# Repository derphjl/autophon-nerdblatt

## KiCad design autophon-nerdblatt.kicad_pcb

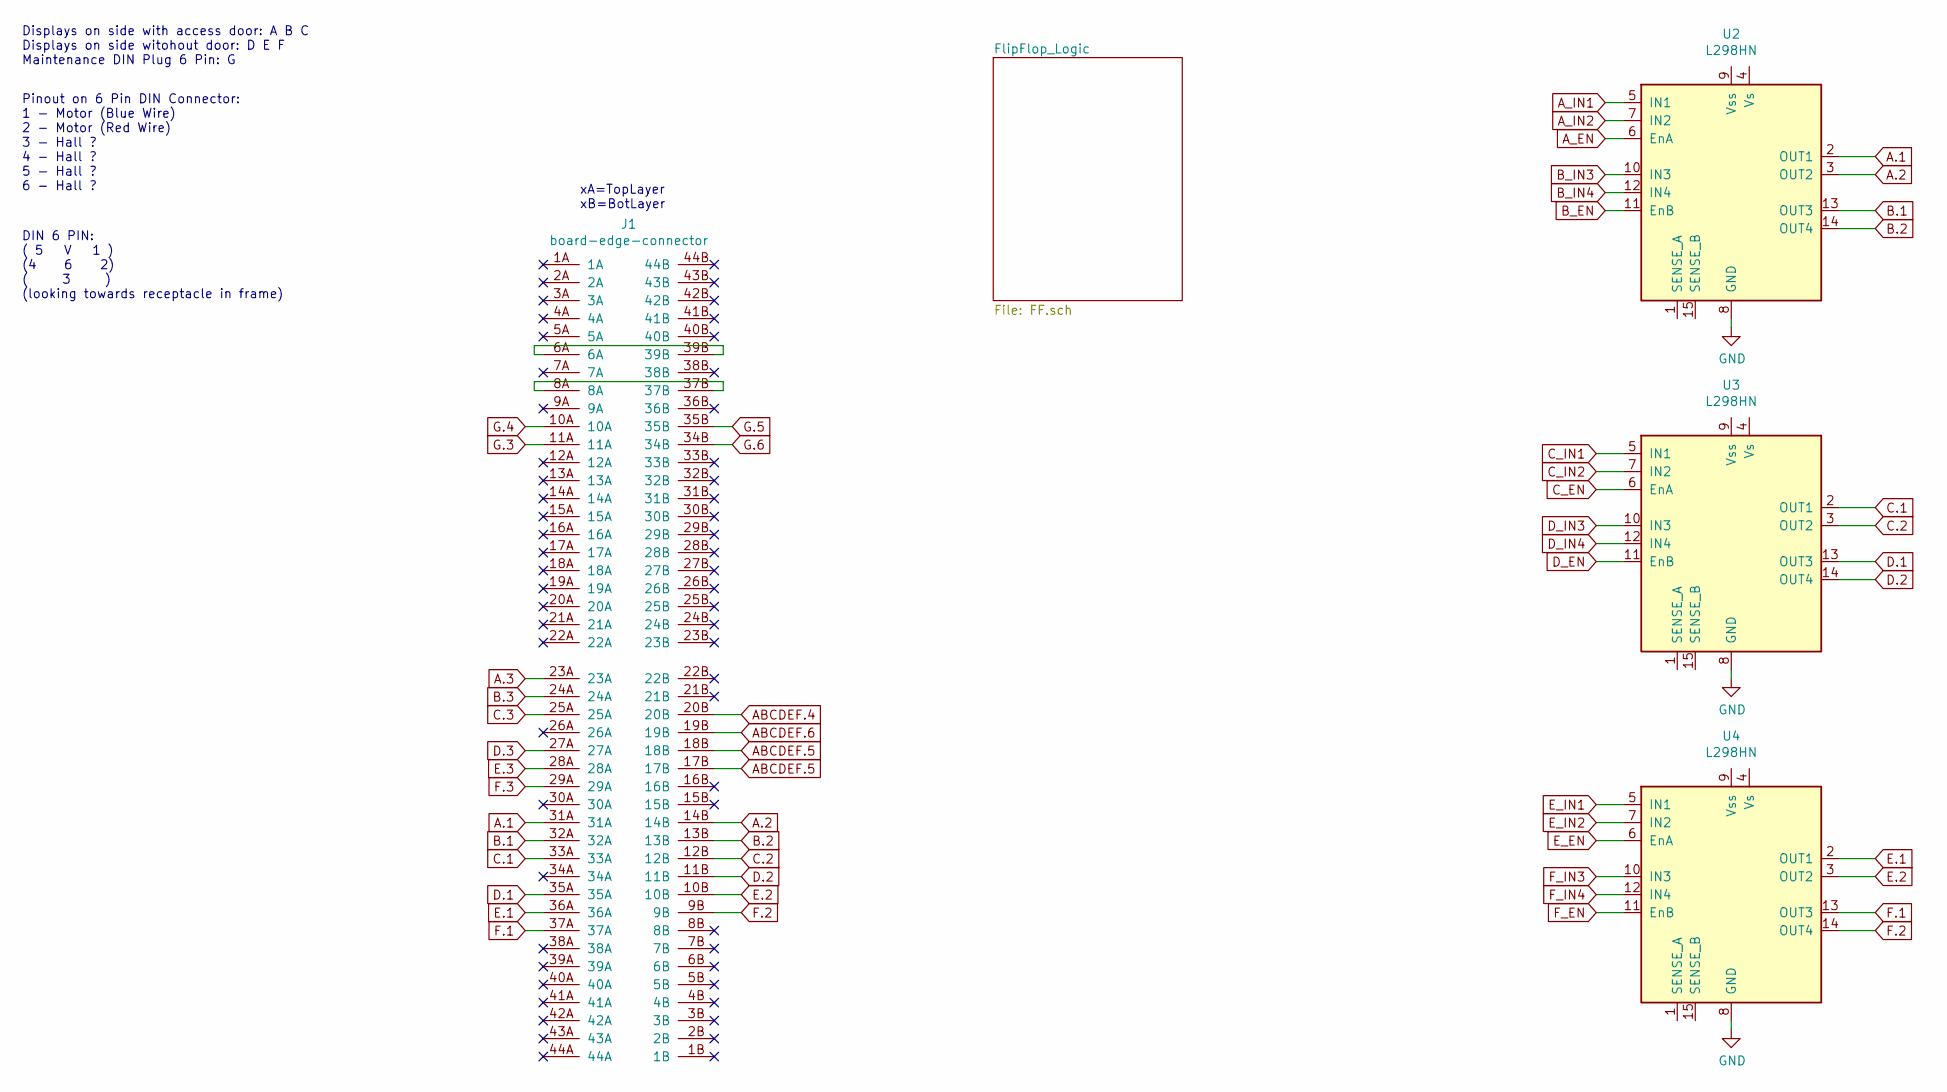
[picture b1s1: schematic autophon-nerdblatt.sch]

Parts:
J1: board-edge-connector; autophon-pcb-edge-connector
U2, U3, U4: L298HN; TO-220F-15_P2.54x5.08mm_StaggerOdd_Lead5.08mm_Vertical

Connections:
A.1: J1.31A, U2.2 (OUT1)
A.2: J1.14B, U2.3 (OUT2)
A.3: J1.23A
ABCDEF.4: J1.20B
ABCDEF.5: J1.17B, J1.18B
ABCDEF.6: J1.19B
A_EN: U2.6 (EnA)
A_IN1: U2.5 (IN1); also elsewhere on the board
A_IN2: U2.7 (IN2); also elsewhere on the board
B.1: J1.32A, U2.13 (OUT3)
B.2: J1.13B, U2.14 (OUT4)
B.3: J1.24A
B_EN: U2.11 (EnB)
B_IN3: U2.10 (IN3); also elsewhere on the board
B_IN4: U2.12 (IN4); also elsewhere on the board
C.1: J1.33A, U3.2 (OUT1)
C.2: J1.12B, U3.3 (OUT2)
C.3: J1.25A
C_EN: U3.6 (EnA)
C_IN1: U3.5 (IN1); also elsewhere on the board
C_IN2: U3.7 (IN2); also elsewhere on the board
D.1: J1.35A, U3.13 (OUT3)
D.2: J1.11B, U3.14 (OUT4)
D.3: J1.27A
D_EN: U3.11 (EnB)
D_IN3: U3.10 (IN3); also elsewhere on the board
D_IN4: U3.12 (IN4); also elsewhere on the board
E.1: J1.36A, U4.2 (OUT1)
E.2: J1.10B, U4.3 (OUT2)
E.3: J1.28A
E_EN: U4.6 (EnA)
E_IN1: U4.5 (IN1); also elsewhere on the board
E_IN2: U4.7 (IN2); also elsewhere on the board
F.1: J1.37A, U4.13 (OUT3)
F.2: J1.9B, U4.14 (OUT4)
F.3: J1.29A
F_EN: U4.11 (EnB)
F_IN3: U4.10 (IN3); also elsewhere on the board
F_IN4: U4.12 (IN4); also elsewhere on the board
G.3: J1.11A
G.4: J1.10A
G.5: J1.35B
G.6: J1.34B
GND: U2.8 (GND), U3.8 (GND), U4.8 (GND); also elsewhere on the board
unnamed: J1.8A, J1.37B
unnamed: J1.6A, J1.39B

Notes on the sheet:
Displays on side with access door: A B C Displays on side witohout door: D E F Maintenance DIN Plug 6 Pin: G
Pinout on 6 Pin DIN Connector: 1 - Motor (Blue Wire) 2 - Motor (Red Wire) 3 - Hall ? 4 - Hall ? 5 - Hall ? 6 - Hall ?
DIN 6 PIN: ( 5 V 1 ) (4 6 2) ( 3 ) (looking towards receptacle in frame)
xA=TopLayer xB=BotLayer

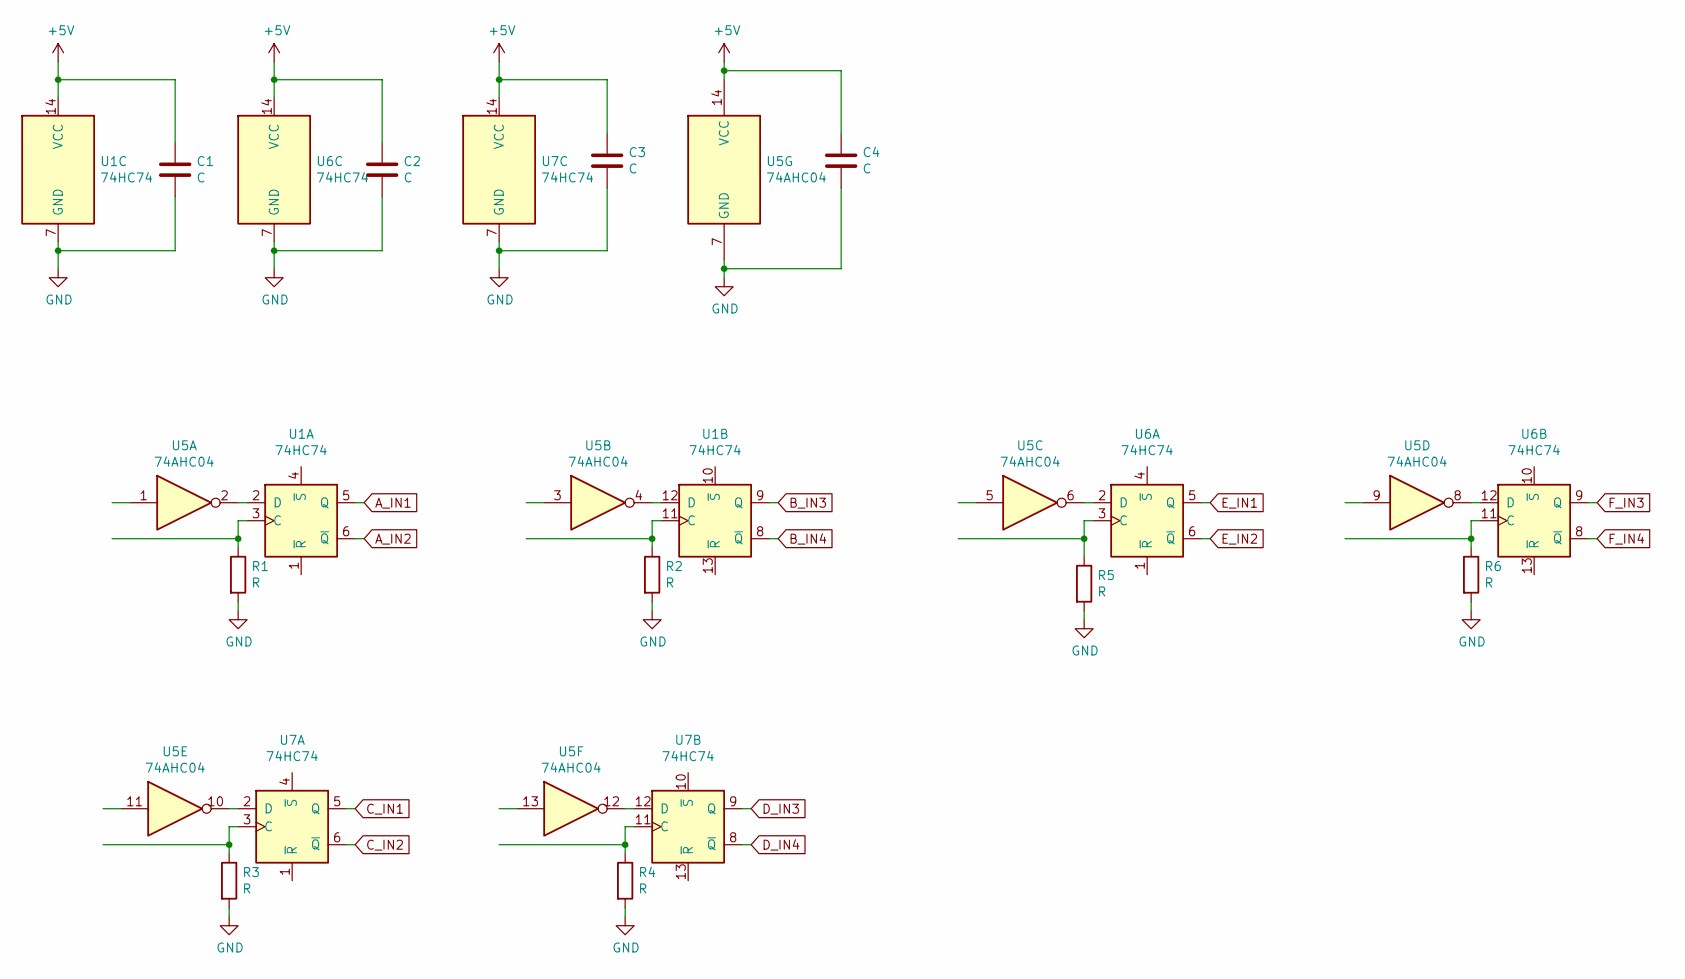
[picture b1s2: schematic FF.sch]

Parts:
C1, C2, C3, C4: C; C_0603_1608Metric
R1, R2, R3, R4, R5, R6: R; R_0603_1608Metric
U1, U6, U7: 74HC74; SO-14_5.3x10.2mm_P1.27mm
U5: 74AHC04; SO-14_5.3x10.2mm_P1.27mm

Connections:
+5V: C1.1, C2.1, C3.1, C4.1, U1.14 (VCC), U5.14 (VCC), U6.14 (VCC), U7.14 (VCC)
A_IN1: U1.5 (Q); also elsewhere on the board
A_IN2: U1.6 (~Q); also elsewhere on the board
B_IN3: U1.9 (Q); also elsewhere on the board
B_IN4: U1.8 (~Q); also elsewhere on the board
C_IN1: U7.5 (Q); also elsewhere on the board
C_IN2: U7.6 (~Q); also elsewhere on the board
D_IN3: U7.9 (Q); also elsewhere on the board
D_IN4: U7.8 (~Q); also elsewhere on the board
E_IN1: U6.5 (Q); also elsewhere on the board
E_IN2: U6.6 (~Q); also elsewhere on the board
F_IN3: U6.9 (Q); also elsewhere on the board
F_IN4: U6.8 (~Q); also elsewhere on the board
GND: C1.2, C2.2, C3.2, C4.2, R1.2, R2.2, R3.2, R4.2, R5.2, R6.2, U1.7 (GND), U5.7 (GND), U6.7 (GND), U7.7 (GND); also elsewhere on the board
unnamed: R1.1, U1.3 (C)
unnamed: R2.1, U1.11 (C)
unnamed: R3.1, U7.3 (C)
unnamed: R4.1, U7.11 (C)
unnamed: R5.1, U6.3 (C)
unnamed: R6.1, U6.11 (C)
unnamed: U1.2 (D), U5.2
unnamed: U1.12 (D), U5.4
unnamed: U5.6, U6.2 (D)
unnamed: U5.8, U6.12 (D)
unnamed: U5.10, U7.2 (D)
unnamed: U5.12, U7.12 (D)

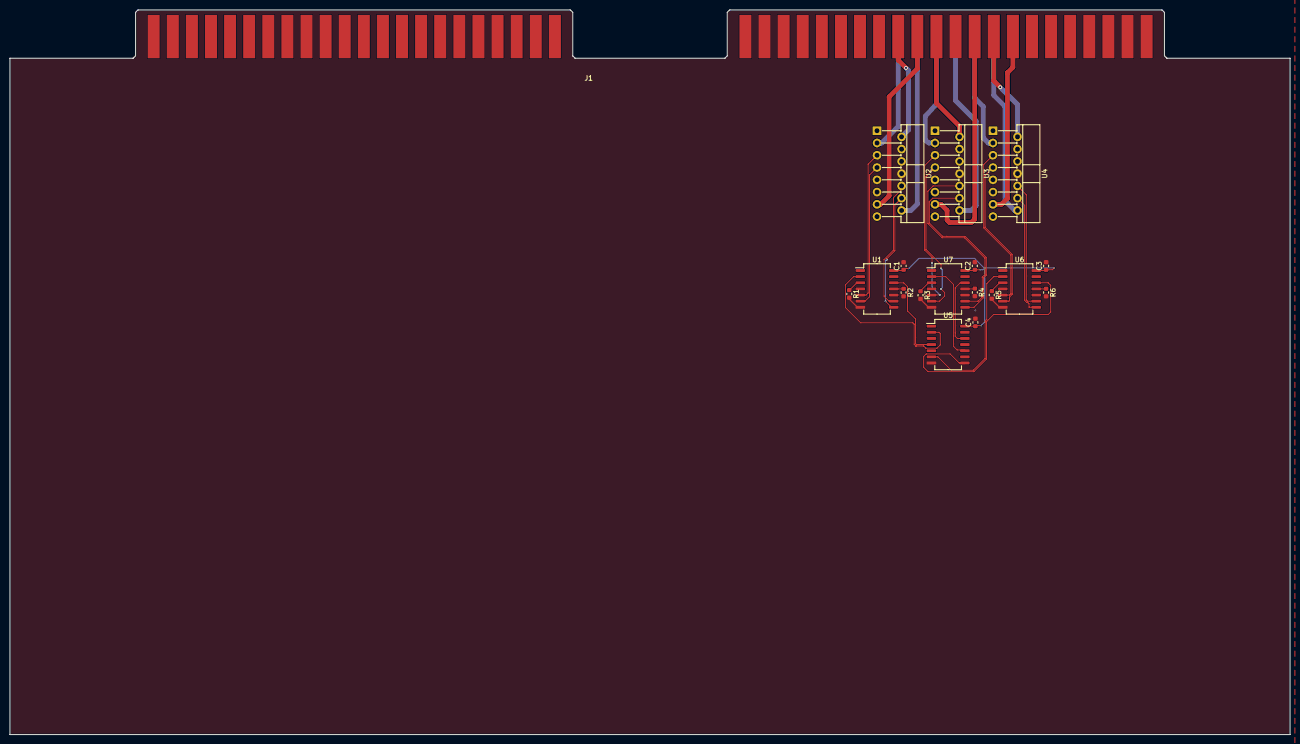
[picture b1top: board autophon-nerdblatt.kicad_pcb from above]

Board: 2 copper layers, 265.0 x 150.0 mm, 18 parts (0 on the bottom side), 41 nets.

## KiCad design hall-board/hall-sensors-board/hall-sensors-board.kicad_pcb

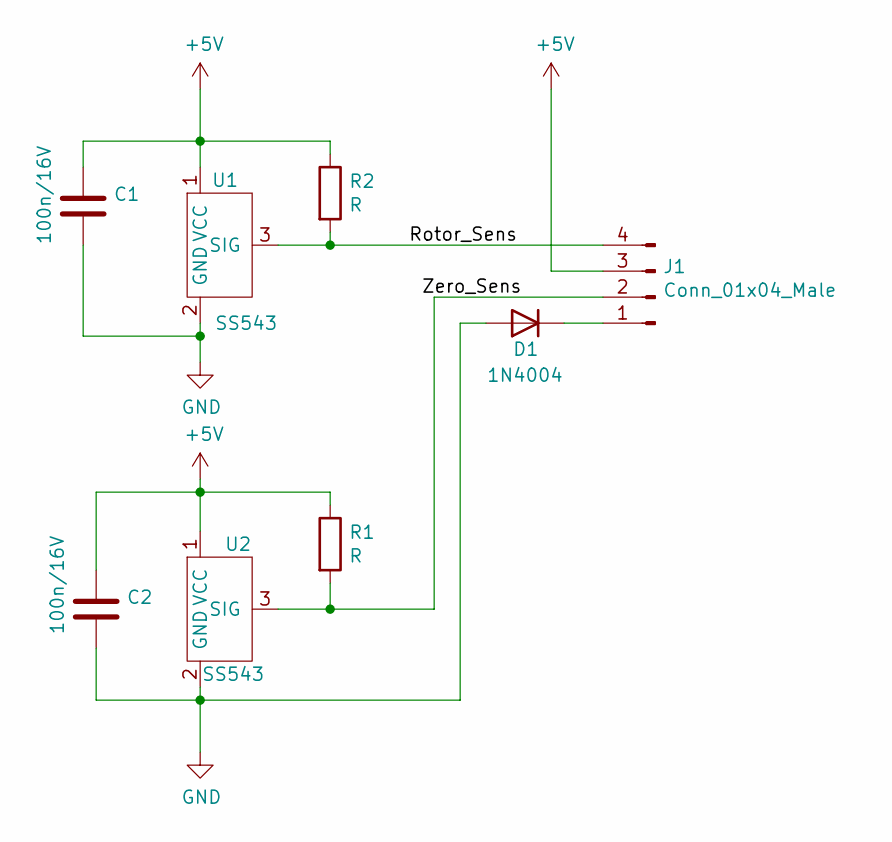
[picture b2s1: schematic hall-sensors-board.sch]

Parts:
C1, C2: 100n/16V; C_0603_1608Metric
D1: 1N4004; D_MELF
J1: Conn_01x04_Male; PinHeader_1x04_P2.54mm_Vertical
R1, R2: R; R_0603_1608Metric
U1, U2: SS543; SOT-89-3

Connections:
+5V: C1.1, C2.1, J1.3, R1.1, R2.1, U1.1 (VCC), U2.1 (VCC)
/Rotor_Sens: J1.4, R2.2, U1.3 (SIG)
GND: C1.2, C2.2, D1.2 (A), U1.2 (GND), U2.2 (GND)
unnamed: D1.1 (K), J1.1
unnamed: J1.2, R1.2, U2.3 (SIG)

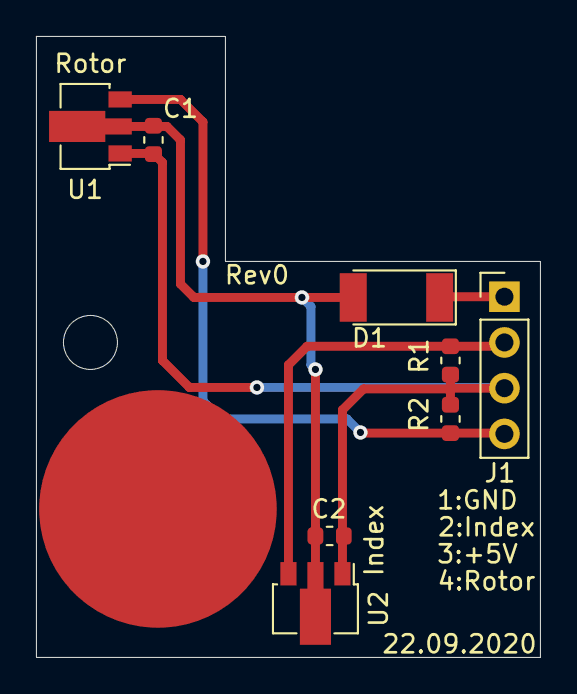
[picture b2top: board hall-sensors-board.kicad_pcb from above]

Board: 2 copper layers, 28.0 x 34.5 mm, 8 parts (0 on the bottom side), 5 nets.

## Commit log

2020-08-02 created autophon-nerdblatt repo
2020-08-03 measured pinout, added lables accordingly
2020-08-03 added DIN 6 pin reference
2020-08-03 changed eco1.user to edge.cuts for pcb edges
2020-08-06 Board Rendering
2020-08-06 Symbol, Footprint improvements. Default Board
2020-09-27 schaltplan aufgeteilt, hallsensorboard erstellt, getestete logic in FF.sch erstellt.
2020-11-30 first Routing of FF
2020-12-04 Thinking.
2020-12-04 add sym-lib table again
2020-12-04 Minor cleanup, adding the w1_test_pcb_lib, just for the single gate buffer.
2020-12-04 Remove FF and "dummy" .sch, add voltage regulators.
